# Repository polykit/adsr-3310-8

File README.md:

# Polykit ADSR-3310-8

Here you can find Kicad schematics and PCB layout for an 8 channel ADSR based on the CEM3310/AS3310 integrated circuit. It has a separate control board for all 4 parameters and offers gate and trigger input and CV output. Power is supplied by standard +12V/-12V Eurorack connector.

## BOM

## Calibration

### ADR

Leave 3310 ICs out and turn attack, decay and release control to maximum. Adjust trimpots until you measure -240mV on all three test points to ground.

### Timing

## References

https://www.synthxl.com/wp-content/uploads/2018/04/Crumar-Trilogy-Schematic.pdf#page=13

https://www.vintagesynthparts.com/wp-content/uploads/2016/08/Crumar-Stratus-Service-Manual.pdf#page=14

http://www.muzines.co.uk/articles/electro-music-engineer-cem-3310/3647

https://www.alfarzpp.lv/eng/sc/AS3310.pdf

https://datasheetspdf.com/pdf-file/104287/ETC/CEM3310/1

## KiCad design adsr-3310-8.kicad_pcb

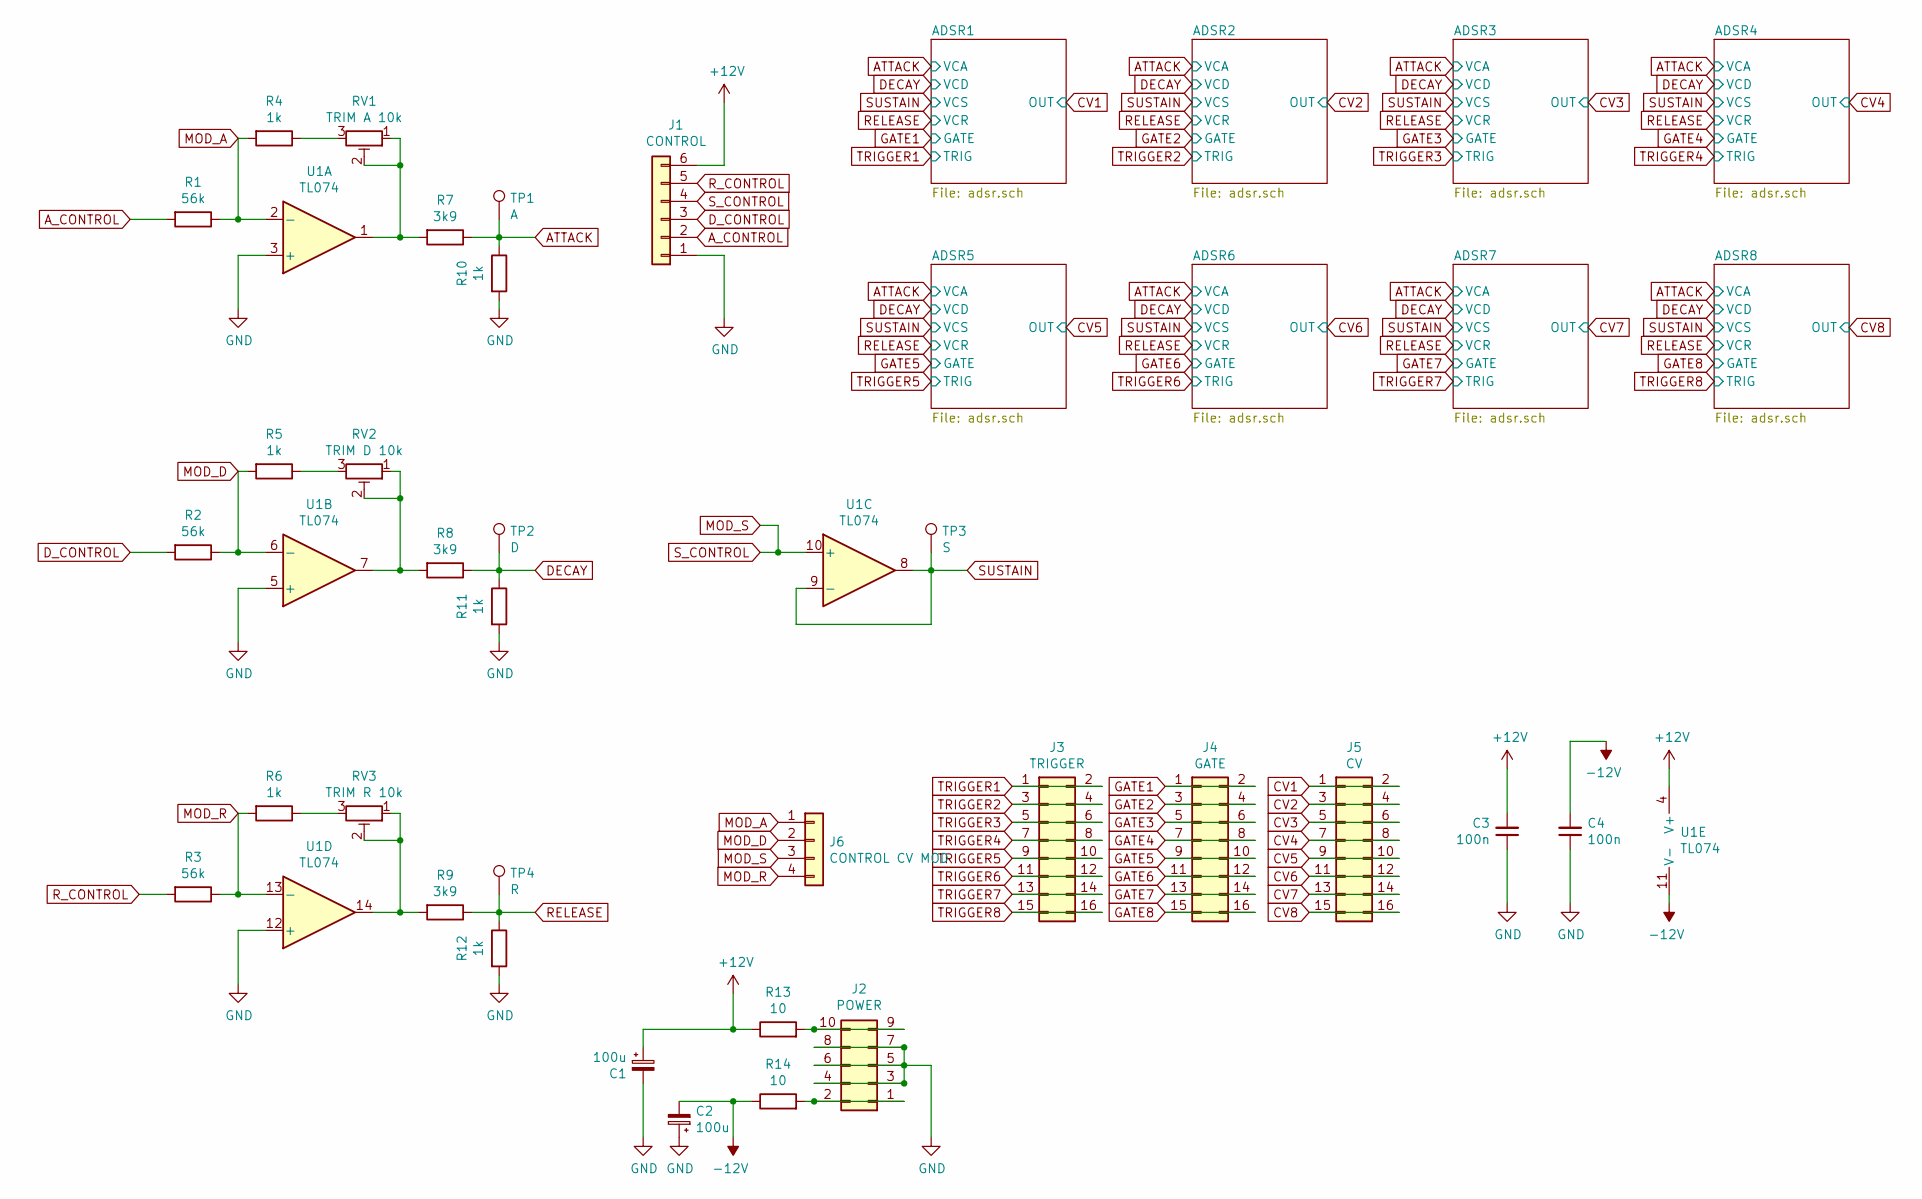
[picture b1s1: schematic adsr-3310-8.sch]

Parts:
C1, C2: 100u; CP_Radial_D6.3mm_P2.50mm
C3, C4: 100n; C_Disc_D3.0mm_W2.0mm_P2.50mm
J1: CONTROL; Molex_KK-254_AE-6410-06A_1x06_P2.54mm_Vertical
J2: POWER; IDC-Header_2x05_P2.54mm_Vertical
J3: TRIGGER; IDC-Header_2x08_P2.54mm_Vertical
J4: GATE; IDC-Header_2x08_P2.54mm_Vertical
J5: CV; IDC-Header_2x08_P2.54mm_Vertical
J6: CONTROL CV MOD; Molex_KK-254_AE-6410-04A_1x04_P2.54mm_Vertical
R1, R2, R3: 56k; R_Axial_DIN0207_L6.3mm_D2.5mm_P10.16mm_Horizontal
R4, R5, R6, R10, R11, R12: 1k; R_Axial_DIN0207_L6.3mm_D2.5mm_P10.16mm_Horizontal
R7, R8, R9: 3k9; R_Axial_DIN0207_L6.3mm_D2.5mm_P10.16mm_Horizontal
R13, R14: 10; R_Axial_DIN0207_L6.3mm_D2.5mm_P10.16mm_Horizontal
RV1: TRIM A 10k; Potentiometer_ACP_CA9-H5_Horizontal
RV2: TRIM D 10k; Potentiometer_ACP_CA9-H5_Horizontal
RV3: TRIM R 10k; Potentiometer_ACP_CA9-H5_Horizontal
TP1: A; TestPoint_Loop_D1.80mm_Drill1.0mm_Beaded
TP2: D; TestPoint_Loop_D1.80mm_Drill1.0mm_Beaded
TP3: S; TestPoint_Loop_D1.80mm_Drill1.0mm_Beaded
TP4: R; TestPoint_Loop_D1.80mm_Drill1.0mm_Beaded
U1: TL074; DIP-14_W7.62mm_Socket_LongPads

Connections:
+12V: C1.1, C3.2, J1.6, R13.1, U1.4 (V+); also elsewhere on the board
-12V: C2.2, C4.2, R14.1, U1.11 (V-); also elsewhere on the board
ATTACK: R7.1, R10.1, TP1.1; also elsewhere on the board
A_CONTROL: J1.2, R1.2
CV1: J5.1, J5.2; also elsewhere on the board
CV2: J5.3, J5.4; also elsewhere on the board
CV3: J5.5, J5.6; also elsewhere on the board
CV4: J5.7, J5.8; also elsewhere on the board
CV5: J5.9, J5.10; also elsewhere on the board
CV6: J5.11, J5.12; also elsewhere on the board
CV7: J5.13, J5.14; also elsewhere on the board
CV8: J5.15, J5.16; also elsewhere on the board
DECAY: R8.1, R11.1, TP2.1; also elsewhere on the board
D_CONTROL: J1.3, R2.2
GATE1: J4.1, J4.2; also elsewhere on the board
GATE2: J4.3, J4.4; also elsewhere on the board
GATE3: J4.5, J4.6; also elsewhere on the board
GATE4: J4.7, J4.8; also elsewhere on the board
GATE5: J4.9, J4.10; also elsewhere on the board
GATE6: J4.11, J4.12; also elsewhere on the board
GATE7: J4.13, J4.14; also elsewhere on the board
GATE8: J4.15, J4.16; also elsewhere on the board
GND: C1.2, C2.1, C3.1, C4.1, J1.1, J2.3, J2.4, J2.5, J2.6, J2.7, J2.8, R10.2, R11.2, R12.2, U1.3 (+), U1.5 (+), U1.12 (+); also elsewhere on the board
MOD_A: J6.1, R1.1, R4.2, U1.2 (-)
MOD_D: J6.2, R2.1, R5.2, U1.6 (-)
MOD_R: J6.4, R3.1, R6.2, U1.13 (-)
MOD_S: J1.4, J6.3, U1.10 (+)
unnamed: J2.1, J2.2, R14.2
unnamed: J2.9, J2.10, R13.2
unnamed: R4.1, RV1.3
unnamed: R5.1, RV2.3
unnamed: R6.1, RV3.3
unnamed: R7.2, RV1.1, RV1.2, U1.1
unnamed: R8.2, RV2.1, RV2.2, U1.7
unnamed: R9.2, RV3.1, RV3.2, U1.14
RELEASE: R9.1, R12.1, TP4.1; also elsewhere on the board
R_CONTROL: J1.5, R3.2
SUSTAIN: TP3.1, U1.8, U1.9 (-); also elsewhere on the board
TRIGGER1: J3.1, J3.2; also elsewhere on the board
TRIGGER2: J3.3, J3.4; also elsewhere on the board
TRIGGER3: J3.5, J3.6; also elsewhere on the board
TRIGGER4: J3.7, J3.8; also elsewhere on the board
TRIGGER5: J3.9, J3.10; also elsewhere on the board
TRIGGER6: J3.11, J3.12; also elsewhere on the board
TRIGGER7: J3.13, J3.14; also elsewhere on the board
TRIGGER8: J3.15, J3.16; also elsewhere on the board

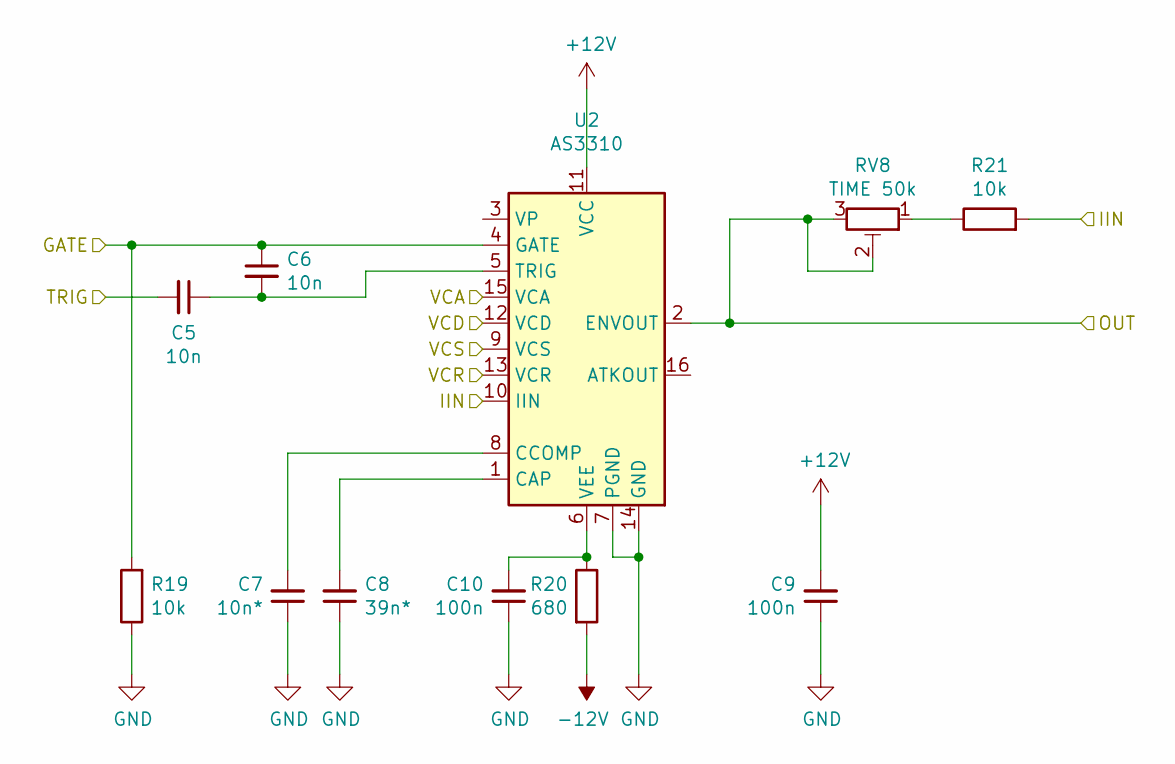
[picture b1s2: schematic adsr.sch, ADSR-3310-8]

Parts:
C5, C6: 10n; C_Disc_D3.0mm_W2.0mm_P2.50mm
C7: 10n*; C_Rect_L7.0mm_W4.5mm_P5.00mm
C8: 39n*; C_Rect_L7.0mm_W4.5mm_P5.00mm
C9, C10: 100n; C_Disc_D3.0mm_W2.0mm_P2.50mm
R19, R21: 10k; R_Axial_DIN0207_L6.3mm_D2.5mm_P10.16mm_Horizontal
R20: 680; R_Axial_DIN0207_L6.3mm_D2.5mm_P10.16mm_Horizontal
RV8: TIME 50k; Potentiometer_ACP_CA9-H5_Horizontal
U2: AS3310; DIP-16_W7.62mm_Socket_LongPads

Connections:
+12V: C9.2, U2.11 (VCC); also elsewhere on the board
-12V: R20.2; also elsewhere on the board
/ADSR1/IIN: R21.2, U2.10 (IIN)
ATTACK: U2.15 (VCA); also elsewhere on the board
CV1: RV8.2, RV8.3, U2.2 (ENVOUT); also elsewhere on the board
DECAY: U2.12 (VCD); also elsewhere on the board
GATE1: C6.1, R19.2, U2.4 (GATE); also elsewhere on the board
GND: C7.1, C8.1, C9.1, C10.1, R19.1, U2.7 (PGND), U2.14 (GND); also elsewhere on the board
unnamed: C5.1, C6.2, U2.5 (TRIG)
unnamed: C7.2, U2.8 (CCOMP)
unnamed: C8.2, U2.1 (CAP)
unnamed: C10.2, R20.1, U2.6 (VEE)
unnamed: R21.1, RV8.1
RELEASE: U2.13 (VCR); also elsewhere on the board
SUSTAIN: U2.9 (VCS); also elsewhere on the board
TRIGGER1: C5.2; also elsewhere on the board

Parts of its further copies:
C11, C12, C17, C18, C23, C24, C29, C30, C35, C36, C41, C42, C47, C48: 10n; C_Disc_D3.0mm_W2.0mm_P2.50mm
C13, C19, C25, C31, C37, C43, C49: 10n*; C_Rect_L7.0mm_W4.5mm_P5.00mm
C14, C20, C26, C32, C38, C44, C50: 39n*; C_Rect_L7.0mm_W4.5mm_P5.00mm
C15, C16, C21, C22, C27, C28, C33, C34, C39, C40, C45, C46, C51, C52: 100n; C_Disc_D3.0mm_W2.0mm_P2.50mm
R15, R17, R18, R23, R24, R26, R27, R29, R30, R32, R33, R35, R36, R38: 10k; R_Axial_DIN0207_L6.3mm_D2.5mm_P10.16mm_Horizontal
R16, R22, R25, R28, R31, R34, R37: 680; R_Axial_DIN0207_L6.3mm_D2.5mm_P10.16mm_Horizontal
RV4, RV5, RV6, RV7, RV9, RV10, RV11: TIME 50k; Potentiometer_ACP_CA9-H5_Horizontal
U3, U4, U5, U6, U7, U8, U9: AS3310; DIP-16_W7.62mm_Socket_LongPads

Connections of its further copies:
+12V: C16.2, C22.2, C28.2, C34.2, C40.2, C46.2, C52.2, U3.11 (VCC), U4.11 (VCC), U5.11 (VCC), U6.11 (VCC), U7.11 (VCC), U8.11 (VCC), U9.11 (VCC); also elsewhere on the board
-12V: R16.2, R22.2, R25.2, R28.2, R31.2, R34.2, R37.2; also elsewhere on the board
/ADSR2/IIN: R17.2, U3.10 (IIN)
/ADSR3/IIN: R23.2, U4.10 (IIN)
/ADSR4/IIN: R26.2, U5.10 (IIN)
/ADSR5/IIN: R29.2, U6.10 (IIN)
/ADSR6/IIN: R32.2, U7.10 (IIN)
/ADSR7/IIN: R35.2, U8.10 (IIN)
/ADSR8/IIN: R38.2, U9.10 (IIN)
ATTACK: U3.15 (VCA), U4.15 (VCA), U5.15 (VCA), U6.15 (VCA), U7.15 (VCA), U8.15 (VCA), U9.15 (VCA); also elsewhere on the board
CV2: RV4.2, RV4.3, U3.2 (ENVOUT); also elsewhere on the board
CV3: RV5.2, RV5.3, U4.2 (ENVOUT); also elsewhere on the board
CV4: RV6.2, RV6.3, U5.2 (ENVOUT); also elsewhere on the board
CV5: RV7.2, RV7.3, U6.2 (ENVOUT); also elsewhere on the board
CV6: RV9.2, RV9.3, U7.2 (ENVOUT); also elsewhere on the board
CV7: RV10.2, RV10.3, U8.2 (ENVOUT); also elsewhere on the board
CV8: RV11.2, RV11.3, U9.2 (ENVOUT); also elsewhere on the board
DECAY: U3.12 (VCD), U4.12 (VCD), U5.12 (VCD), U6.12 (VCD), U7.12 (VCD), U8.12 (VCD), U9.12 (VCD); also elsewhere on the board
GATE2: C12.1, R15.2, U3.4 (GATE); also elsewhere on the board
GATE3: C18.1, R18.2, U4.4 (GATE); also elsewhere on the board
GATE4: C24.1, R24.2, U5.4 (GATE); also elsewhere on the board
GATE5: C30.1, R27.2, U6.4 (GATE); also elsewhere on the board
GATE6: C36.1, R30.2, U7.4 (GATE); also elsewhere on the board
GATE7: C42.1, R33.2, U8.4 (GATE); also elsewhere on the board
GATE8: C48.1, R36.2, U9.4 (GATE); also elsewhere on the board
GND: C13.1, C14.1, C15.1, C16.1, C19.1, C20.1, C21.1, C22.1, C25.1, C26.1, C27.1, C28.1, C31.1, C32.1, C33.1, C34.1, C37.1, C38.1, C39.1, C40.1, C43.1, C44.1, C45.1, C46.1, C49.1, C50.1, C51.1, C52.1, R15.1, R18.1, R24.1, R27.1, R30.1, R33.1, R36.1, U3.7 (PGND), U3.14 (GND), U4.7 (PGND), U4.14 (GND), U5.7 (PGND), U5.14 (GND), U6.7 (PGND), U6.14 (GND), U7.7 (PGND), U7.14 (GND), U8.7 (PGND), U8.14 (GND), U9.7 (PGND), U9.14 (GND); also elsewhere on the board
unnamed: C11.1, C12.2, U3.5 (TRIG)
unnamed: C13.2, U3.8 (CCOMP)
unnamed: C14.2, U3.1 (CAP)
unnamed: C15.2, R16.1, U3.6 (VEE)
unnamed: C17.1, C18.2, U4.5 (TRIG)
unnamed: C19.2, U4.8 (CCOMP)
unnamed: C20.2, U4.1 (CAP)
unnamed: C21.2, R22.1, U4.6 (VEE)
unnamed: C23.1, C24.2, U5.5 (TRIG)
unnamed: C25.2, U5.8 (CCOMP)
unnamed: C26.2, U5.1 (CAP)
unnamed: C27.2, R25.1, U5.6 (VEE)
unnamed: C29.1, C30.2, U6.5 (TRIG)
unnamed: C31.2, U6.8 (CCOMP)
unnamed: C32.2, U6.1 (CAP)
unnamed: C33.2, R28.1, U6.6 (VEE)
unnamed: C35.1, C36.2, U7.5 (TRIG)
unnamed: C37.2, U7.8 (CCOMP)
unnamed: C38.2, U7.1 (CAP)
unnamed: C39.2, R31.1, U7.6 (VEE)
unnamed: C41.1, C42.2, U8.5 (TRIG)
unnamed: C43.2, U8.8 (CCOMP)
unnamed: C44.2, U8.1 (CAP)
unnamed: C45.2, R34.1, U8.6 (VEE)
unnamed: C47.1, C48.2, U9.5 (TRIG)
unnamed: C49.2, U9.8 (CCOMP)
unnamed: C50.2, U9.1 (CAP)
unnamed: C51.2, R37.1, U9.6 (VEE)
unnamed: R17.1, RV4.1
unnamed: R23.1, RV5.1
unnamed: R26.1, RV6.1
unnamed: R29.1, RV7.1
unnamed: R32.1, RV9.1
unnamed: R35.1, RV10.1
unnamed: R38.1, RV11.1
RELEASE: U3.13 (VCR), U4.13 (VCR), U5.13 (VCR), U6.13 (VCR), U7.13 (VCR), U8.13 (VCR), U9.13 (VCR); also elsewhere on the board
SUSTAIN: U3.9 (VCS), U4.9 (VCS), U5.9 (VCS), U6.9 (VCS), U7.9 (VCS), U8.9 (VCS), U9.9 (VCS); also elsewhere on the board
TRIGGER2: C11.2; also elsewhere on the board
TRIGGER3: C17.2; also elsewhere on the board
TRIGGER4: C23.2; also elsewhere on the board
TRIGGER5: C29.2; also elsewhere on the board
TRIGGER6: C35.2; also elsewhere on the board
TRIGGER7: C41.2; also elsewhere on the board
TRIGGER8: C47.2; also elsewhere on the board

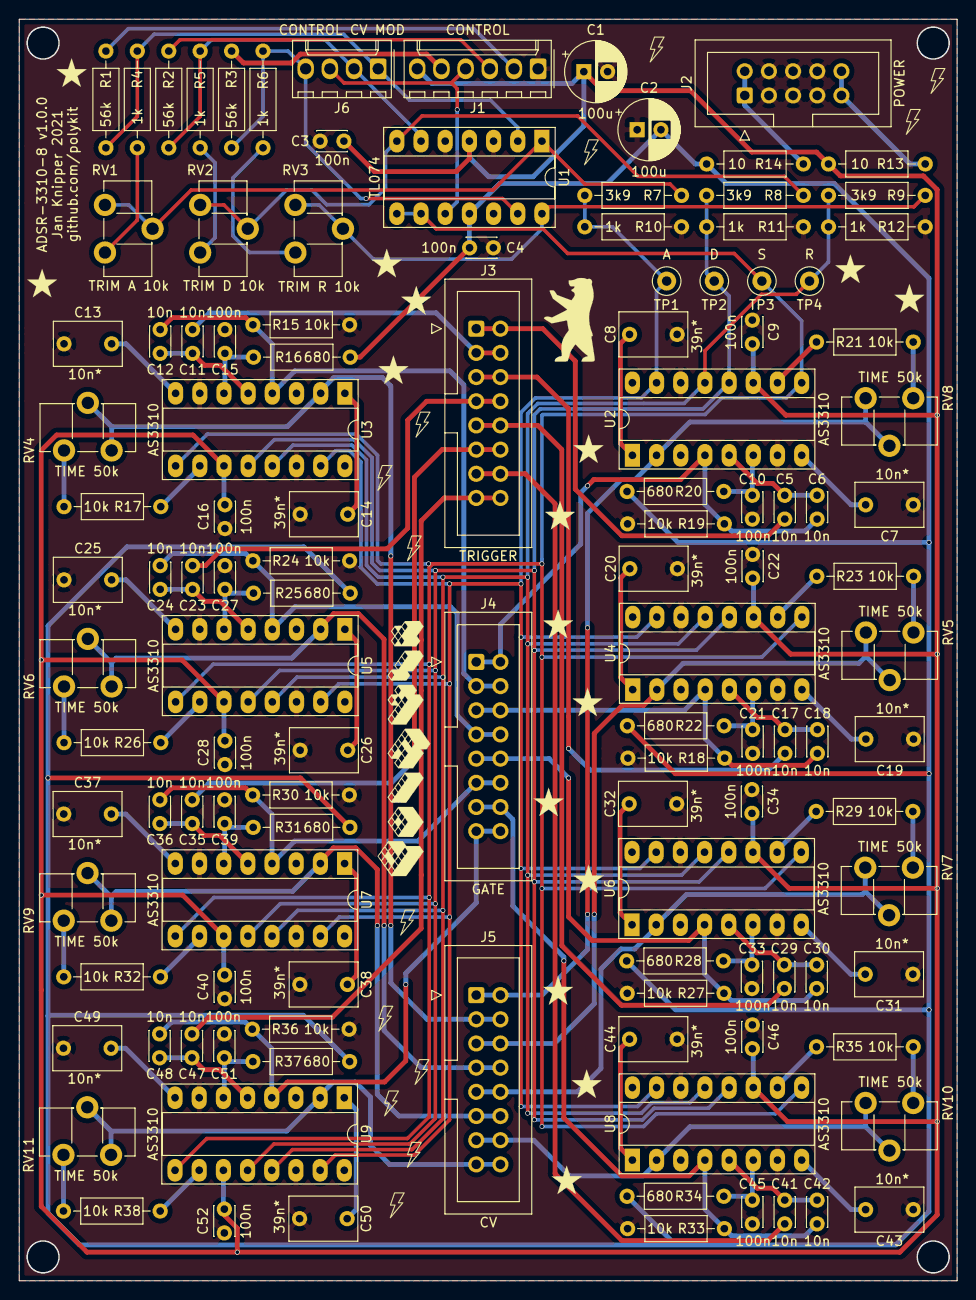
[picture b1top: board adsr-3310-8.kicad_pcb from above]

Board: 2 copper layers, 98.5 x 132.5 mm, 120 parts (0 on the bottom side), 94 nets.

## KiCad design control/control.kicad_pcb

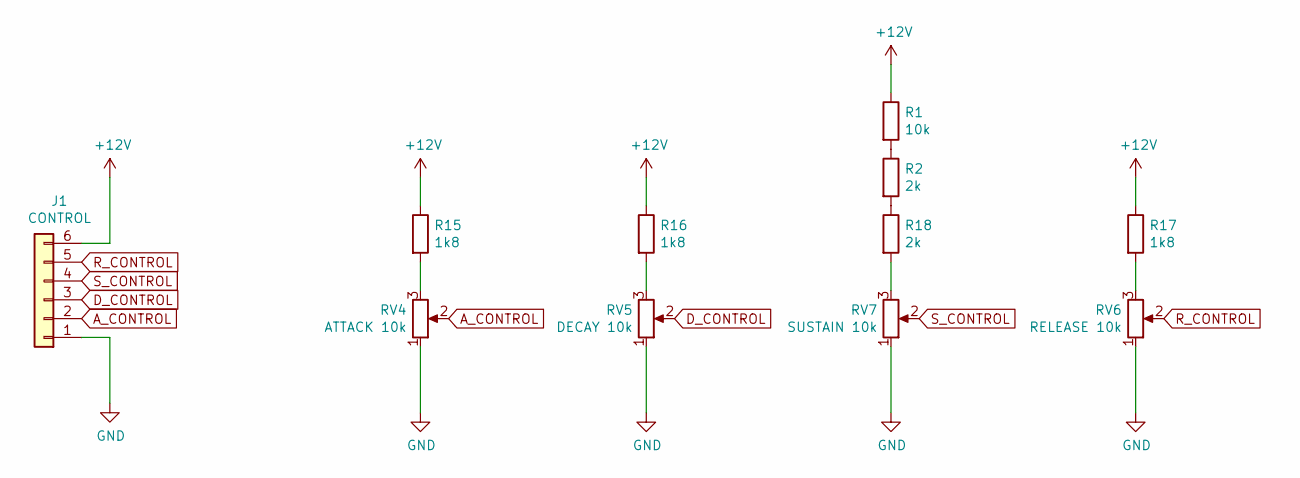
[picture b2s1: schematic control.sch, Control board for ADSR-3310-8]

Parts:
J1: CONTROL; Molex_KK-254_AE-6410-06A_1x06_P2.54mm_Vertical
R1: 10k; R_Axial_DIN0207_L6.3mm_D2.5mm_P10.16mm_Horizontal
R2, R18: 2k; R_Axial_DIN0207_L6.3mm_D2.5mm_P10.16mm_Horizontal
R15, R16, R17: 1k8; R_Axial_DIN0207_L6.3mm_D2.5mm_P10.16mm_Horizontal
RV4: ATTACK 10k; Potentiometer_Alpha_RD901F-40-00D_Single_Vertical
RV5: DECAY 10k; Potentiometer_Alpha_RD901F-40-00D_Single_Vertical
RV6: RELEASE 10k; Potentiometer_Alpha_RD901F-40-00D_Single_Vertical
RV7: SUSTAIN 10k; Potentiometer_Alpha_RD901F-40-00D_Single_Vertical

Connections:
+12V: J1.6, R1.1, R15.1, R16.1, R17.1
A_CONTROL: J1.2, RV4.2
D_CONTROL: J1.3, RV5.2
GND: J1.1, RV4.1, RV5.1, RV6.1, RV7.1
unnamed: R1.2, R2.1
unnamed: R15.2, RV4.3
unnamed: R16.2, RV5.3
unnamed: R17.2, RV6.3
unnamed: R2.2, R18.1
unnamed: R18.2, RV7.3
R_CONTROL: J1.5, RV6.2
S_CONTROL: J1.4, RV7.2

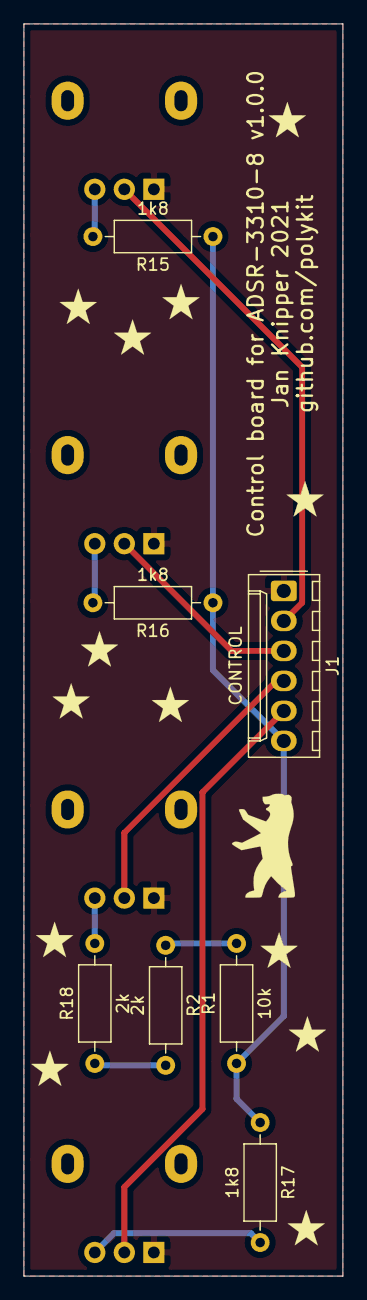
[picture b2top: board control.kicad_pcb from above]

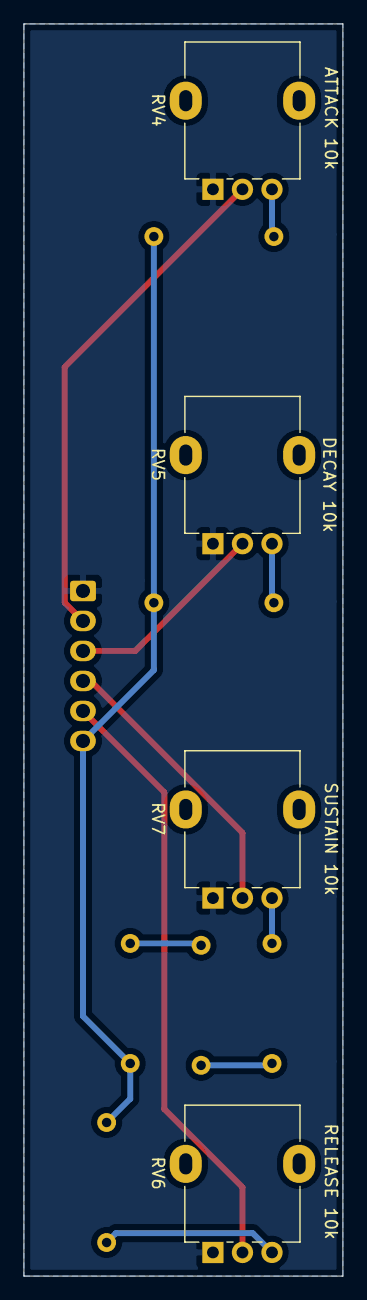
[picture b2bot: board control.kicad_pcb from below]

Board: 2 copper layers, 27.0 x 106.0 mm, 11 parts (4 on the bottom side), 12 nets.

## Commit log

2021-11-06 Initial import
